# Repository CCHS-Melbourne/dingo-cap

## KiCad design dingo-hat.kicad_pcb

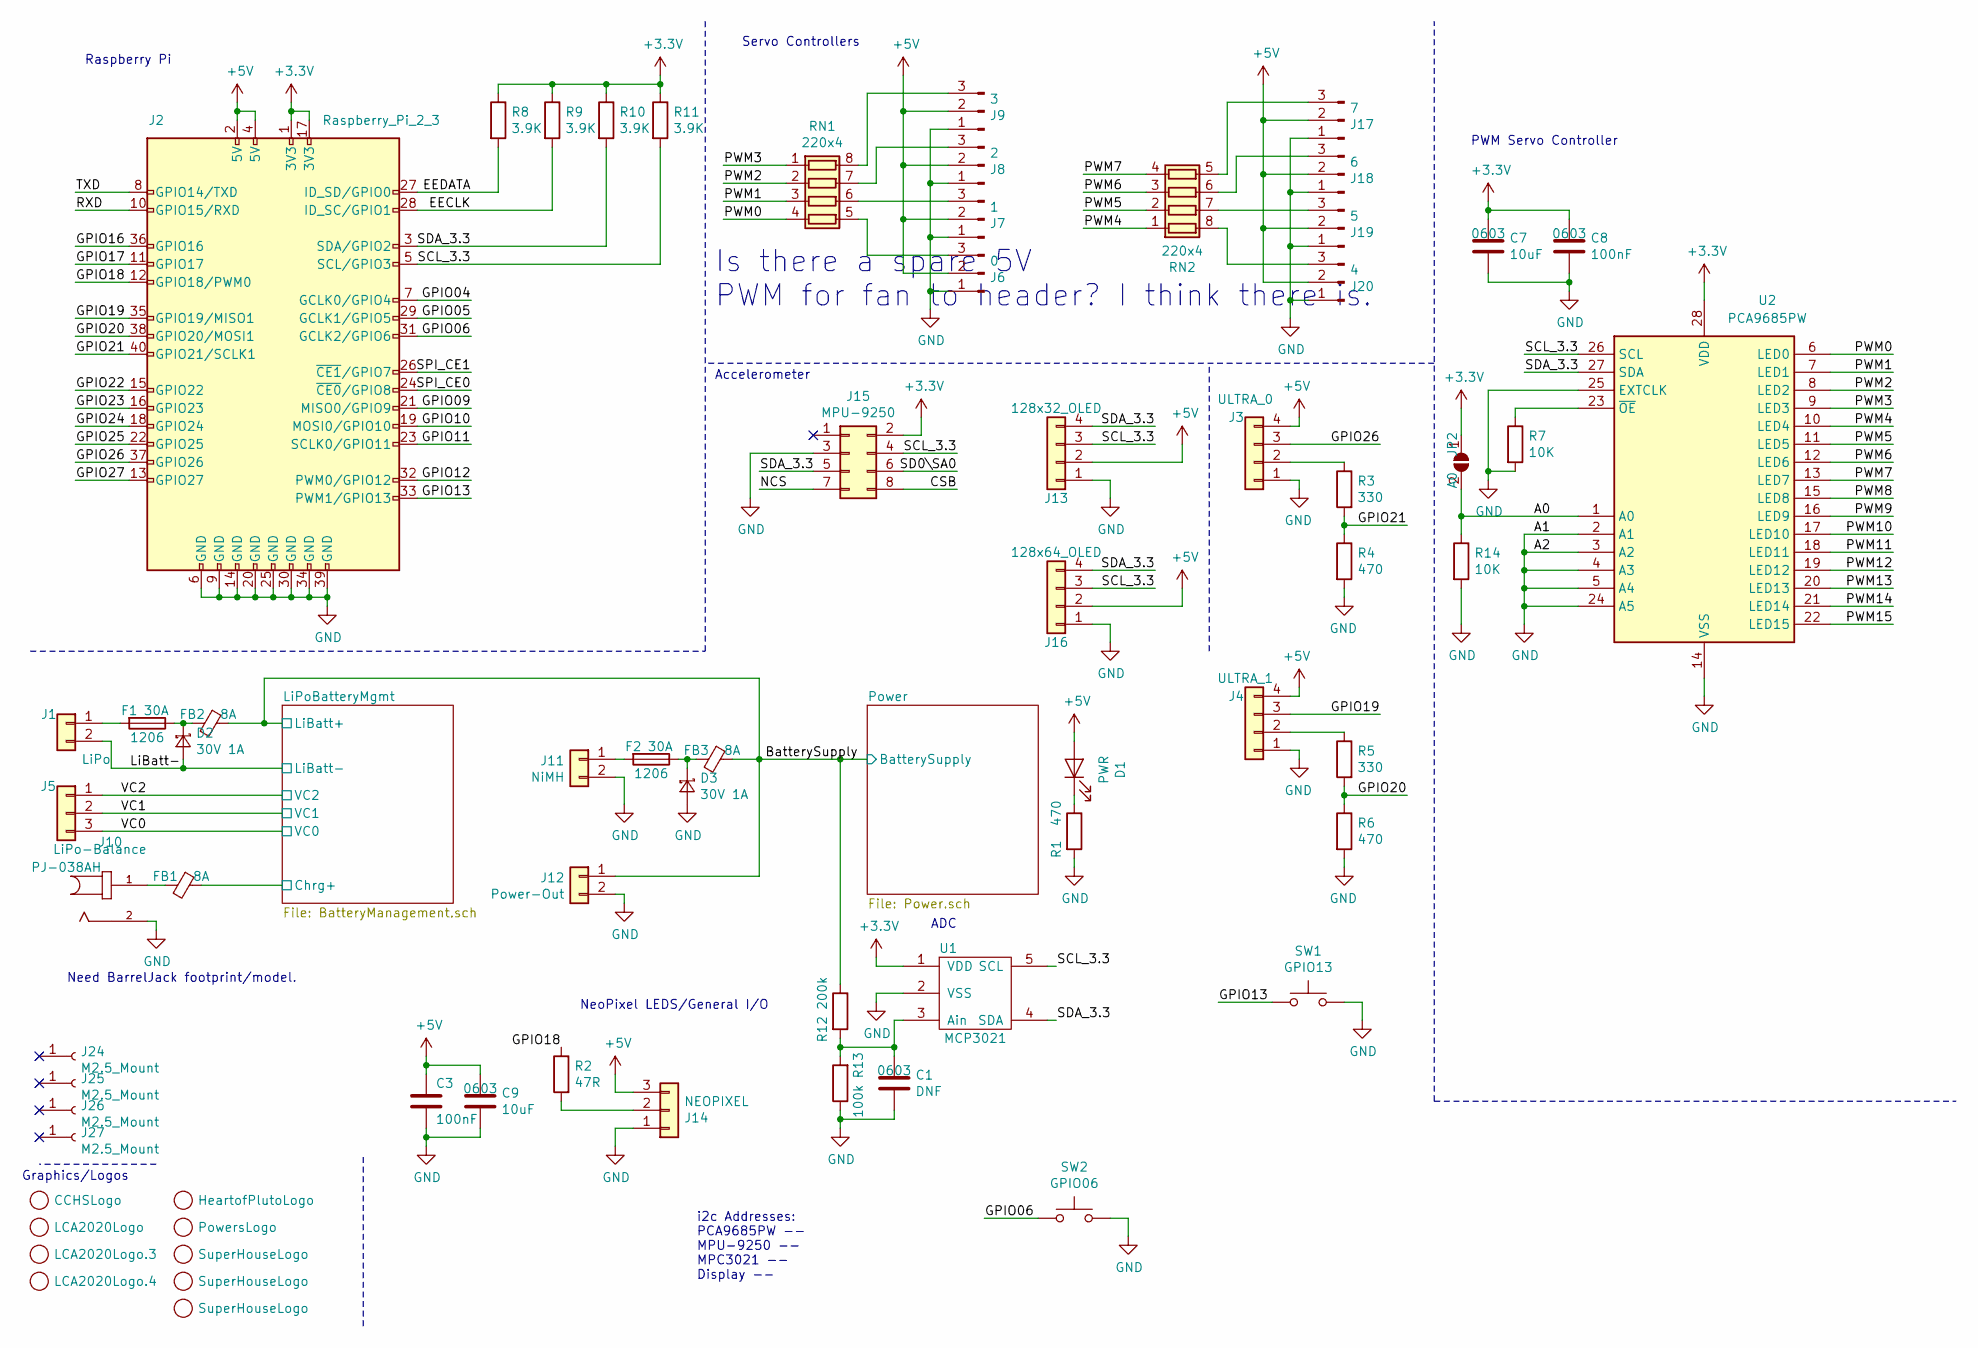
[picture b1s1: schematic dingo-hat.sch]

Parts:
C1: DNF; C_0603_1608Metric_Pad1.05x0.95mm_HandSolder; Voltage Rating 50V
C3: 100nF; R_0603_1608Metric_Pad1.05x0.95mm_HandSolder; Voltage Rating 50V
C7: 10uF; C_0603_1608Metric_Pad1.05x0.95mm_HandSolder
C8: 100nF; C_0603_1608Metric_Pad1.05x0.95mm_HandSolder; Voltage Rating 50V
C9: 10uF; R_0603_1608Metric_Pad1.05x0.95mm_HandSolder
D1: PWR; LED_0603_1608Metric_Pad1.05x0.95mm_HandSolder
D2, D3: 30V 1A; D_SOD-123F; Voltage Rating 30V
F1, F2: Fuse; R_1206_3216Metric_Pad1.42x1.75mm_HandSolder; Voltage Rating 32V
FB1, FB2, FB3: Ferrite_Bead_Small; R_0603_1608Metric_Pad1.05x0.95mm_HandSolder
G1: CCHSLogo; logo.cchs
G2: LCA2020Logo; logo.LCA.2020.1
G3: HeartofPlutoLogo; logo.HeartOfPluto2
G4: LCA2020Logo.3; logo-2020.silk
G5: LCA2020Logo.4; logo-2020.mask
G6: PowersLogo; logo.pc
G7: SuperHouseLogo; logo.superhouse
G8, G9: SuperHouseLogo; logo.dingocar
J1: LiPo; SolderWirePad_2x_5.08mm_14-18AWG-2mmDrill
J2: Raspberry_Pi_2_3; PinSocket_2x20_P2.54mm_Vertical
J3: ULTRA_0; Pin_Header_Straight_1x04_Pitch2.54mm
J4: ULTRA_1; Pin_Header_Straight_1x04_Pitch2.54mm
J5: LiPo-Balance; JST_XH_S03B-XH-A_03x2.50mm_Angled
J6: 0; PinHeader_1x03_P2.54mm_Vertical
J7: 1; PinHeader_1x03_P2.54mm_Vertical
J8: 2; PinHeader_1x03_P2.54mm_Vertical
J9: 3; PinHeader_1x03_P2.54mm_Vertical
J10: PJ-038AH; CUI_PJ-038AH; Mfg Part # PJ-038AH
J11: NiMH; SolderWirePad_2x_5.08mm_14-18AWG-2mmDrill
J12: Power-Out; SolderWirePad_2x_5.08mm_14-18AWG-2mmDrill
J13: 128x32_OLED; 0.91 OLED
J14: NEOPIXEL; PinHeader_1x03_P2.54mm_Vertical
J15: MPU-9250; PinHeader_1x08_P2.54mm_Vertical
J16: 128x64_OLED
J17: 7; PinHeader_1x03_P2.54mm_Vertical
J18: 6; PinHeader_1x03_P2.54mm_Vertical
J19: 5; PinHeader_1x03_P2.54mm_Vertical
J20: 4; PinHeader_1x03_P2.54mm_Vertical
J24, J25, J26, J27: M2.5_Mount; MountingHole_2.7mm_M2.5
JP2: A0; SolderJumper-2_P1.3mm_Open_RoundedPad1.0x1.5mm
R1: 470; R_0603_1608Metric_Pad1.05x0.95mm_HandSolder
R2: 47R; R_0603_1608Metric_Pad1.05x0.95mm_HandSolder
R3, R5: 330; R_0603_HandSoldering
R4, R6: 470; R_0603_HandSoldering
R7, R14: 10K; R_0603_1608Metric_Pad1.05x0.95mm_HandSolder
R8, R9, R10, R11: 3.9K; R_0603_1608Metric_Pad1.05x0.95mm_HandSolder
R12: 200k; R_0603_1608Metric_Pad1.05x0.95mm_HandSolder
R13: 100k; R_0603_1608Metric_Pad1.05x0.95mm_HandSolder
RN1, RN2: 220x4; R_Array_Convex_4x0603
SW1: GPIO13; SW_PUSH_4.5mm
SW2: GPIO06; SW_PUSH_4.5mm
U1: MCP3021; SOT-23-5; Mfg Part # MCP3021A5T-E/OT
U2: PCA9685PW; TSSOP-28_4.4x9.7mm_P0.65mm; Mfg Part # PCA9685

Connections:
+3V3: C7.1, C8.1, J2.1 (3V3), J2.17 (3V3), J15.2, JP2.1 (A), R8.1, R9.1, R10.1, R11.1, U1.1 (VDD), U2.28 (VDD)
+5V: C3.1, C9.1, D1.2 (A), J2.2 (5V), J2.4 (5V), J3.4, J4.4, J6.2, J7.2, J8.2, J9.2, J13.2, J14.3, J16.2, J17.2, J18.2, J19.2, J20.2; also elsewhere on the board
/A0: JP2.2 (B), R14.1, U2.1 (A0)
/BatterySupply: FB2.1, FB3.1, J12.1, R12.1; also elsewhere on the board
/CSB: J15.8
/EECLK: J2.28 (ID_SC/GPIO1), R9.2
/EEDATA: J2.27 (ID_SD/GPIO0), R8.2
/GPIO04: J2.7 (GCLK0/GPIO4)
/GPIO05: J2.29 (GCLK1/GPIO5)
/GPIO06: J2.31 (GCLK2/GPIO6), SW2.1
/GPIO09: J2.21 (MISO0/GPIO9)
/GPIO10: J2.19 (MOSI0/GPIO10)
/GPIO11: J2.23 (SCLK0/GPIO11)
/GPIO12: J2.32 (PWM0/GPIO12)
/GPIO13: J2.33 (PWM1/GPIO13), SW1.1
/GPIO16: J2.36 (GPIO16)
/GPIO17: J2.11 (GPIO17)
/GPIO18: J2.12 (GPIO18/PWM0), R2.1
/GPIO19: J2.35 (GPIO19/MISO1), J4.3
/GPIO20: J2.38 (GPIO20/MOSI1), R5.2, R6.1
/GPIO21: J2.40 (GPIO21/SCLK1), R3.2, R4.1
/GPIO22: J2.15 (GPIO22)
/GPIO23: J2.16 (GPIO23)
/GPIO24: J2.18 (GPIO24)
/GPIO25: J2.22 (GPIO25)
/GPIO26: J2.37 (GPIO26), J3.3
/GPIO27: J2.13 (GPIO27)
/LiPoBatteryMgmt/Chrg+: FB1.1; also elsewhere on the board
/NCS: J15.7
/PWM0: RN1.4 (R4.1), U2.6 (LED0)
/PWM1: RN1.3 (R3.1), U2.7 (LED1)
/PWM2: RN1.2 (R2.1), U2.8 (LED2)
/PWM3: RN1.1 (R1.1), U2.9 (LED3)
/PWM4: RN2.1 (R1.1), U2.10 (LED4)
/PWM5: RN2.2 (R2.1), U2.11 (LED5)
/PWM6: RN2.3 (R3.1), U2.12 (LED6)
/PWM7: RN2.4 (R4.1), U2.13 (LED7)
/PWM8: U2.15 (LED8)
/PWM9: U2.16 (LED9)
/PWM10: U2.17 (LED10)
/PWM11: U2.18 (LED11)
/PWM12: U2.19 (LED12)
/PWM13: U2.20 (LED13)
/PWM14: U2.21 (LED14)
/PWM15: U2.22 (LED15)
/RXD: J2.10 (GPIO15/RXD)
/SCL_3.3: J2.5 (SCL/GPIO3), J13.3, J15.4, J16.3, R11.2, U1.5 (SCL), U2.26 (SCL)
/SD0\SA0: J15.6
/SDA_3.3: J2.3 (SDA/GPIO2), J13.4, J15.5, J16.4, R10.2, U1.4 (SDA), U2.27 (SDA)
/SPI_CE0: J2.24 (~CE0~/GPIO8)
/SPI_CE1: J2.26 (~CE1~/GPIO7)
/TXD: J2.8 (GPIO14/TXD)
/VC0: J5.3; also elsewhere on the board
/VC1: J5.2; also elsewhere on the board
/VC2: J5.1; also elsewhere on the board
GND: C1.2, C3.2, C7.2, C8.2, C9.2, D2.2 (A), D3.2 (A), J1.2, J2.6 (GND), J2.9 (GND), J2.14 (GND), J2.20 (GND), J2.25 (GND), J2.30 (GND), J2.34 (GND), J2.39 (GND), J3.1, J4.1, J6.1, J7.1, J8.1, J9.1, J10.2, J11.2, J12.2, J13.1, J14.1, J15.3, J16.1, J17.1, J18.1, J19.1, J20.1, R1.2, R4.2, R6.2, R7.2, R13.1, R14.2, SW1.2, SW2.2, U1.2 (VSS), U2.2 (A1), U2.3 (A2), U2.4 (A3), U2.5 (A4), U2.14 (VSS), U2.24 (A5), U2.25 (EXTCLK); also elsewhere on the board
unnamed: C1.1, R12.2, R13.2, U1.3 (Ain)
unnamed: D1.1 (K), R1.1
unnamed: D2.1 (K), F1.1, FB2.2
unnamed: D3.1 (K), F2.1, FB3.2
unnamed: F1.2, J1.1
unnamed: F2.2, J11.1
unnamed: FB1.2, J10.1
unnamed: J3.2, R3.1
unnamed: J4.2, R5.1
unnamed: J6.3, RN1.5 (R4.2)
unnamed: J7.3, RN1.6 (R3.2)
unnamed: J8.3, RN1.7 (R2.2)
unnamed: J9.3, RN1.8 (R1.2)
unnamed: J14.2, R2.2
unnamed: J17.3, RN2.5 (R4.2)
unnamed: J18.3, RN2.6 (R3.2)
unnamed: J19.3, RN2.7 (R2.2)
unnamed: J20.3, RN2.8 (R1.2)
unnamed: R7.1, U2.23 (~OE)

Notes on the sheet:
PWM Servo Controller
NeoPixel LEDS/General I/O
Servo Controllers
Raspberry Pi
Accelerometer
Graphics/Logos
ADC
i2c Addresses: PCA9685PW -- MPU-9250 -- MPC3021 -- Display --
Need BarrelJack footprint/model.
Is there a spare 5V PWM for fan to header? I think there is.

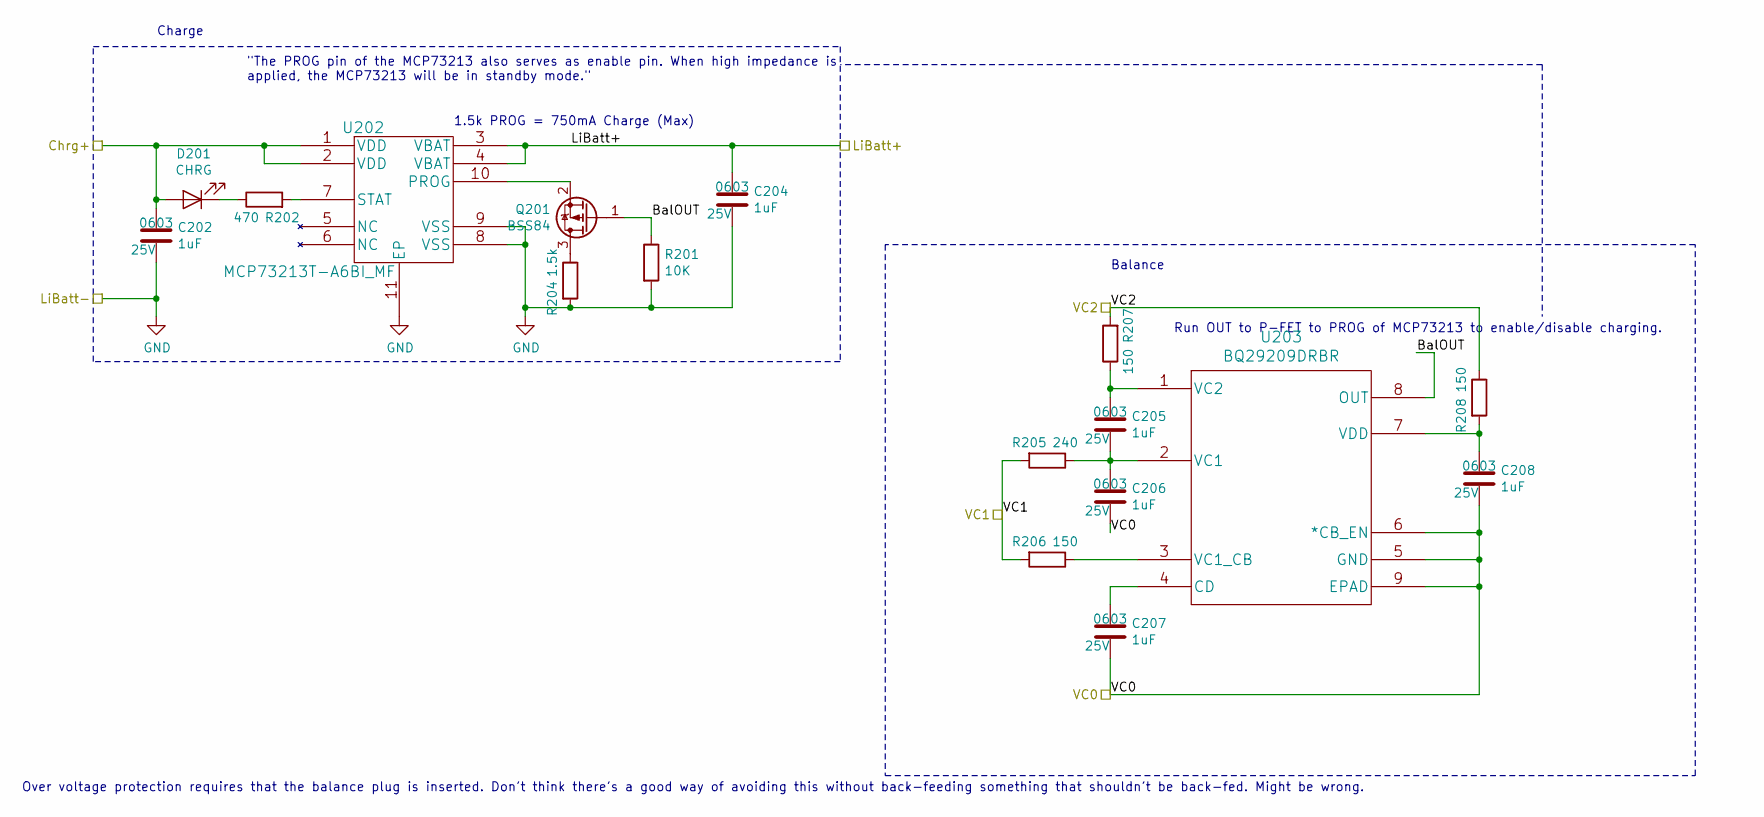
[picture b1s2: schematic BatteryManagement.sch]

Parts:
C202, C204, C205, C206, C207, C208: 1uF; C_0603_1608Metric_Pad1.05x0.95mm_HandSolder; Voltage Rating 25V
D201: CHRG; LED_0603_1608Metric_Pad1.05x0.95mm_HandSolder
Q201: BSS84; SOT-23
R201: 10K; R_0603_1608Metric_Pad1.05x0.95mm_HandSolder
R202: 470; R_0603_1608Metric_Pad1.05x0.95mm_HandSolder
R204: 1.5k; R_0603_1608Metric_Pad1.05x0.95mm_HandSolder
R205: 240; R_0603_1608Metric_Pad1.05x0.95mm_HandSolder
R206, R207, R208: 150; R_0603_1608Metric_Pad1.05x0.95mm_HandSolder
U202: MCP73213T-A6BI_MF; MCP73213T-A6BI
U203: BQ29209DRBR; Mfg Part # BQ29209DRBR

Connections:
/BatterySupply: C204.1, U202.3 (VBAT), U202.4 (VBAT); also elsewhere on the board
/LiPoBatteryMgmt/BalOUT: Q201.1 (G), R201.1, U203.8 (OUT)
/LiPoBatteryMgmt/Chrg+: C202.1, D201.2 (A), U202.1 (VDD), U202.2 (VDD); also elsewhere on the board
/VC0: C206.2, C207.2, C208.2, U203.5 (GND), U203.6 (*CB_EN), U203.9 (EPAD); also elsewhere on the board
/VC1: R205.2, R206.2; also elsewhere on the board
/VC2: R207.2, R208.1; also elsewhere on the board
GND: C202.2, C204.2, R201.2, R204.2, U202.8 (VSS), U202.9 (VSS), U202.11 (EP); also elsewhere on the board
unnamed: C205.1, R207.1, U203.1 (VC2)
unnamed: C205.2, C206.1, R205.1, U203.2 (VC1)
unnamed: C207.1, U203.4 (CD)
unnamed: C208.1, R208.2, U203.7 (VDD)
unnamed: D201.1 (K), R202.1
unnamed: Q201.2 (S), U202.10 (PROG)
unnamed: Q201.3 (D), R204.1
unnamed: R202.2, U202.7 (STAT)
unnamed: R206.1, U203.3 (VC1_CB)

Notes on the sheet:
1.5k PROG = 750mA Charge (Max)
Run OUT to P-FET to PROG of MCP73213 to enable/disable charging.
Balance
Charge
"The PROG pin of the MCP73213 also serves as enable pin. When high impedance is applied, the MCP73213 will be in standby mode."
Over voltage protection requires that the balance plug is inserted. Don't think there's a good way of avoiding this without back-feeding something that shouldn't be back-fed. Might be wrong.

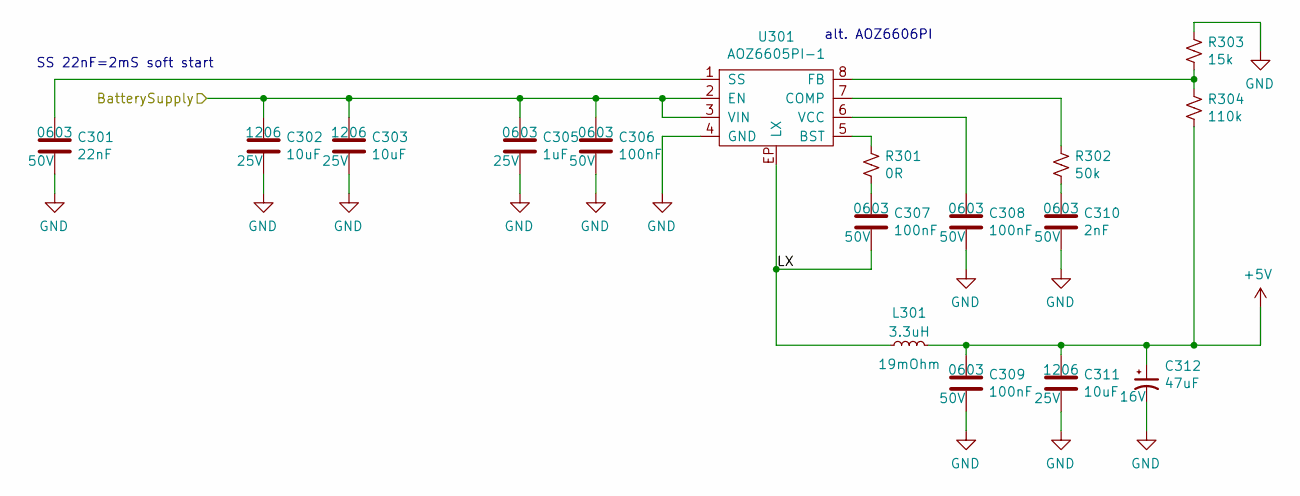
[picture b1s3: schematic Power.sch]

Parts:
C301: 22nF; C_0603_1608Metric_Pad1.05x0.95mm_HandSolder; Voltage Rating 50V
C302, C303, C311: 10uF; C_1206_3216Metric_Pad1.42x1.75mm_HandSolder; Voltage Rating 25V
C305: 1uF; C_0603_1608Metric_Pad1.05x0.95mm_HandSolder; Voltage Rating 25V
C306, C307, C308, C309: 100nF; C_0603_1608Metric_Pad1.05x0.95mm_HandSolder; Voltage Rating 50V
C310: 2nF; C_0603_1608Metric_Pad1.05x0.95mm_HandSolder; Voltage Rating 50V
C312: 47uF; CP_Elec_6.6x6.6; Voltage Rating 16V
L301: 3.3uH; Inductor-SMT-MPLCH0740
R301: 0R; R_0603_1608Metric_Pad1.05x0.95mm_HandSolder
R302: 50k; R_0603_1608Metric_Pad1.05x0.95mm_HandSolder
R303: 15k; R_0603_1608Metric_Pad1.05x0.95mm_HandSolder
R304: 110k; R_0603_1608Metric_Pad1.05x0.95mm_HandSolder
U301: AOZ6605PI-1; SOIC-8-EP--AOZ6605PI-1; Mfg Part # AOZ6605PI-1

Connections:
+5V: C309.1, C311.1, C312.1, L301.2, R304.2; also elsewhere on the board
/BatterySupply: C302.1, C303.1, C305.1, C306.1, U301.2 (EN), U301.3 (VIN); also elsewhere on the board
/Power/LX: C307.2, L301.1, U301.EP (LX)
GND: C301.2, C302.2, C303.2, C305.2, C306.2, C308.2, C309.2, C310.2, C311.2, C312.2, R303.1, U301.4 (GND); also elsewhere on the board
unnamed: C301.1, U301.1 (SS)
unnamed: C307.1, R301.1
unnamed: C308.1, U301.6 (VCC)
unnamed: C310.1, R302.1
unnamed: R301.2, U301.5 (BST)
unnamed: R302.2, U301.7 (COMP)
unnamed: R303.2, R304.1, U301.8 (FB)

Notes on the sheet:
alt. AOZ6606PI
SS 22nF=2mS soft start

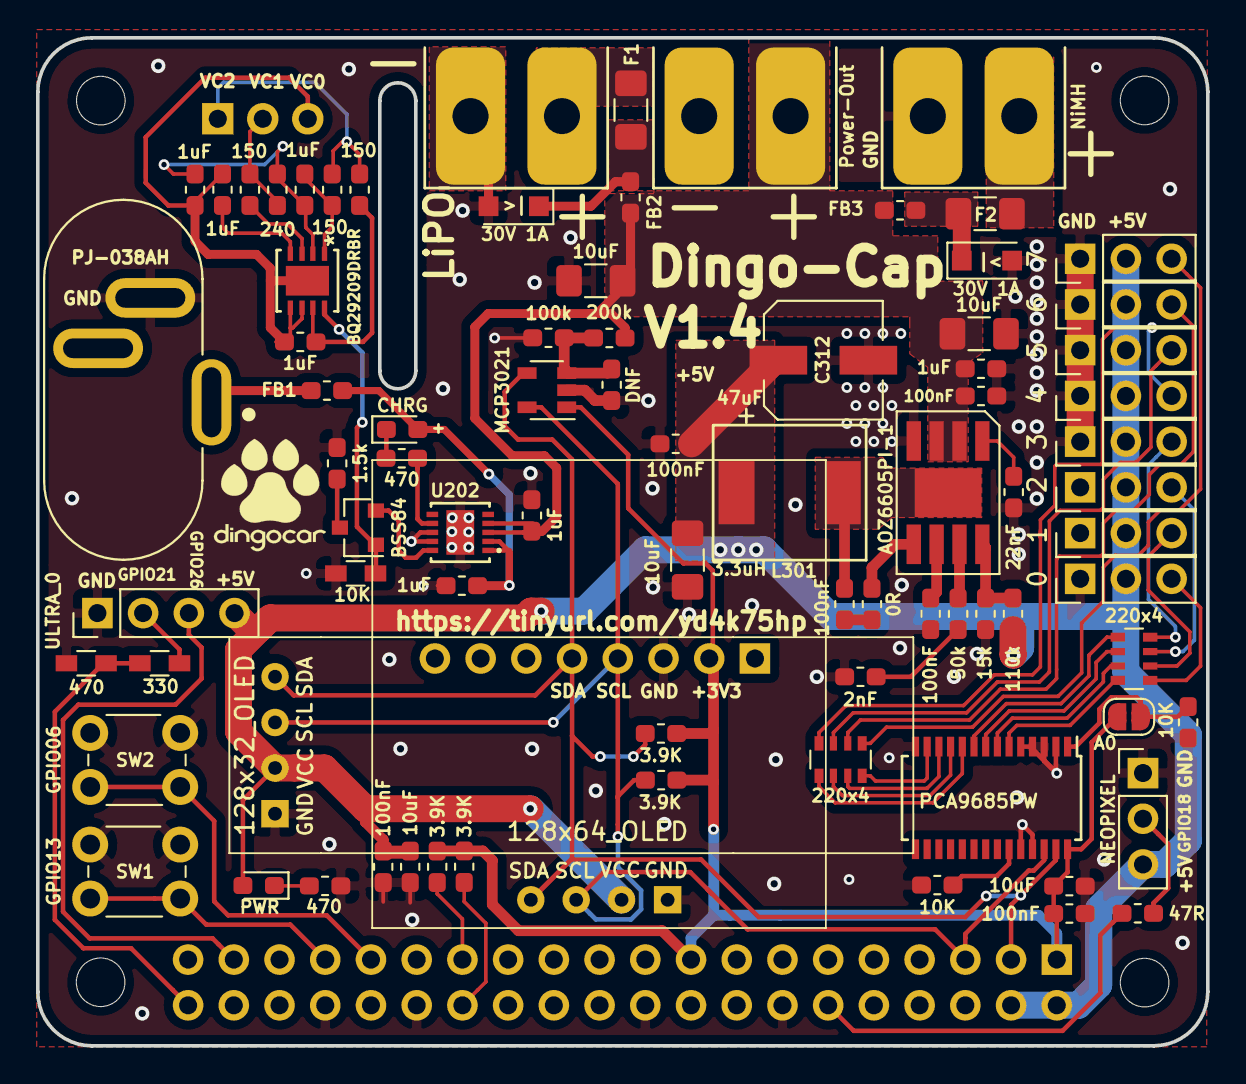
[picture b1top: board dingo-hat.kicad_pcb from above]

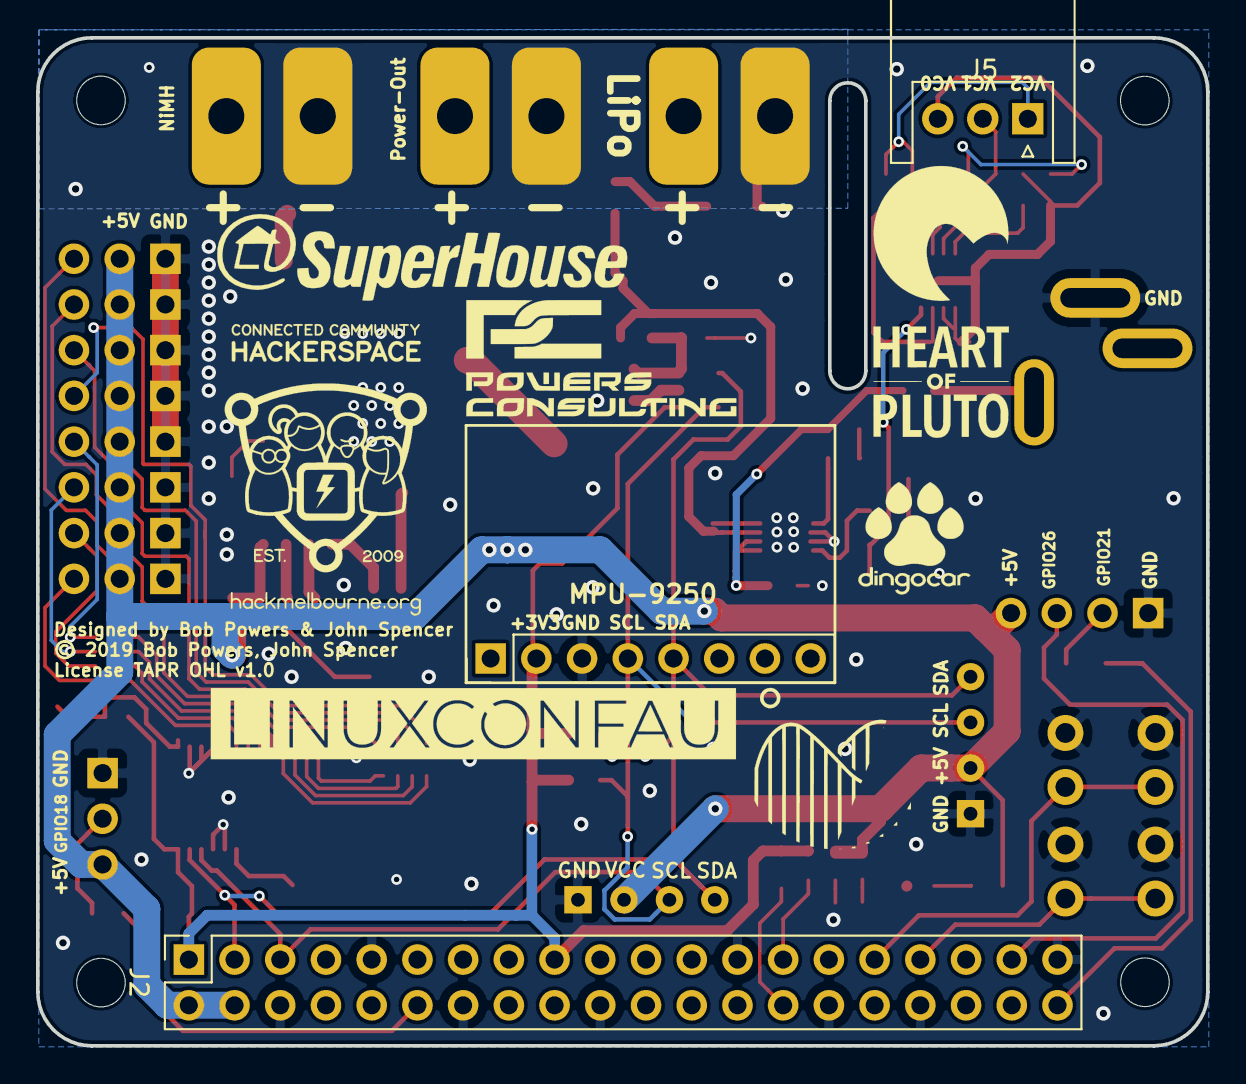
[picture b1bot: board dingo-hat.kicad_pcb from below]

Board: 2 copper layers, 65.0 x 56.0 mm, 98 parts (11 on the bottom side), 62 nets.

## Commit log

2019-10-14 Edge.Cut drawings for Dingo-Hat
2019-10-17 Cleaning up libs. Looking at power.
2019-10-19 Setting up fields, more structure, touching up schematic display properties.
2019-10-19 Decisions on DCDC, adding components.
2019-10-23 Doing schematic of DCDC.
2019-10-23 Starting battery protection & management.
2019-10-23 Changing structure, RM old power circuitry.
2019-10-24 Battery work, need to get on to connectors.
2019-10-24 Charging. Do balance next if including.
2019-10-25 Balance IC lib & footprint.
2019-10-25 Battery circuitry nearly done. Look at charge enable.
2019-10-25 Adding ADC for battery level.
2019-10-25 Getting rid of address block on PCA9685. We don't need that many options.
2019-10-25 Create 0.91 OLED.kicad_mod
    Footprint for the 0.91 OLED we plan to use.
2019-10-26 Removed 4 of the Servo pins
    We only need 4.
2019-10-26 Added i2c header
2019-10-29 Placeholders for some connectors.
2019-10-29 Cleaning up some nets, adding input caps on power.
2019-10-29 Changing net names on balance charger.
2019-10-29 Self notes.
2019-10-31 Power protection.
2019-10-31 Filling in some footprints, cleaning up schematic.
2019-10-31 Adding barrel jack, models.
2019-10-31 Cleaning up schematics.
2019-10-31 Chaging lib table. Going to push sch to pcb.
2019-10-31 Cleaning up the component links.
2019-10-31 First revision of LCA Logo 2020
2019-10-31 Doing some back and forth on initial placements. Remove address options for PWM.
2019-10-31 Trying out layout, modifying solder pad footprint.
2019-10-31 Some blocks of layout.
2019-10-31 Pushing and shoving components.
2019-10-31 Just moving that PWM controller back from the edge.
2019-10-31 Updated logos
    Updated the CCHS logo and added a new one for Linux.conf.au 2020
2019-10-31 Updated for the logo.
2019-11-01 Compacting blocks of layout.
2019-11-01 Starting power fills.
2019-11-01 Power net fill routing.
2019-11-01 Pushing things around. Routing. Major current paths done.
2019-11-01 Needs cleaning up, but most routing done.
2019-11-03 Updated Silkscreen.
2019-11-03 Minor tweaks to overlay.
2019-11-04 Adding top pour to balance CU. Gerbers.
2019-11-05 This should be the prototype production version v1.0. Tag HERE.
2019-11-05 Moving everything so origin is at an round point.
2019-11-05 Removing errant astrisk on U202. Closes #2.
2019-11-06 Updated footprints
2019-11-06 Changed and re-routed to be 2 layer
2019-11-15 updated footprints to handsolder
2019-11-20 Included both oled and MPU on top. Additional silkscreen designs
2019-11-22 Updated silkscreen. Added button
2019-11-23 Minor updates to hopefully make soldering easier.
2019-11-25 Changing MCP73213 footprint to recommended dimensions. Need to update board to close issue.
2019-11-26 Tweaks to footprint alignment.
2019-11-26 New V.1.2 gerbers
2019-11-27 Updating loop compensation values with asperational attempt.
2019-11-27 Fixing glitch in 6-UDFN footprint.
2019-11-27 Fixing up Li protection IC, update some fills. Relief on protection IC.
2019-11-27 Closes #19 - MCP footprint already updated. Adding calcs spreadsheet referenced in Issue #14.
2019-11-27 Direct pad connect rear GND power pads.
2019-12-02 Remove the LiPo OC protection, fuse & RP will be sufficient when used with balance & charge OV cutoff. That change is in here too. Closes #17, closes #22.
2019-12-02 Changing barrel jack to be 2.1ID, 5.5OD. Needs double check to close issue (28).
2019-12-05 Change mounting holes to M2.5. Closes #29.
2019-12-05 Cleaning up, flipped JST balance. Closes #21.
2019-12-05 Added second header for OLED referenced in #25, need to place. Added model for barrel jack - may not be perfectly aligned.
2019-12-05 Flipping around the PWM header, making room for moving DC/DC.
2019-12-05 Ripping up, re-placing lots of stuff to make more room.
2019-12-05 Smushing everything left to make room for that electrolytic as mentioned in #24
2019-12-05 More compacting, improvement on space utilization. Closes #24.
2019-12-06 Flipping IMU to back of board.
2019-12-07 IMU now properly flipped.
2019-12-07 Trying to add in the ultrasonics, other bits.
2019-12-07 Maybe just re-layout the whole thing.
2019-12-07 Compactifying the balance circuit, making heaps of space.
2019-12-07 Most things in place, thinking about adding power button, other buttons.
2019-12-07 Routed with dual oled
    Single Ultrasonic has made it back. Yay!
2019-12-07 Added logos
2019-12-08 Added 4 extra PWM. Reroute.
    Also flipped design to be up the right way for our chassis.
2019-12-08 Generated Gerbers for 1.4 version
2019-12-08 Changing labels, adding vias, tweaking.
2019-12-08 More minor tweaks. Nearly done.
2019-12-08 Minor updates to overlays.
2019-12-08 Candidate v1.4 production files.
2019-12-09 Regenerating gerbers candidate v1.4.

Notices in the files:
dingo-hat.kicad_pcb:
© 2019 Bob Powers, John Spencer
parts and their libraries:
Copyright 2016 Accelerated Designs. All rights reserved.
